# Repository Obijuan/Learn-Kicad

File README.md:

# Learn-Kicad
My notes about Kicad

# WIKI

You can find the Development log in the

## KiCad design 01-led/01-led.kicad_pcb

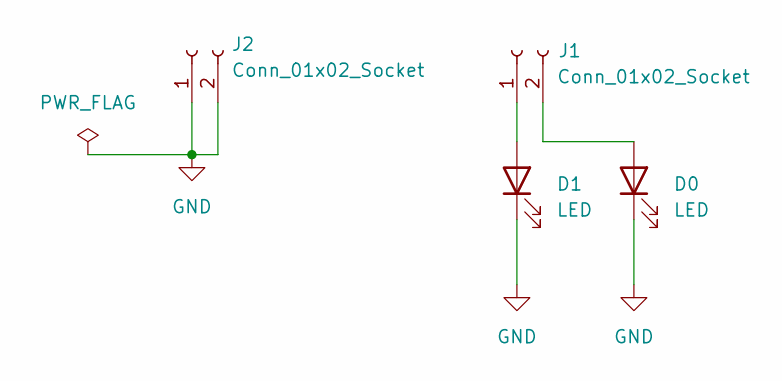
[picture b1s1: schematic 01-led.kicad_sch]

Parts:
D0, D1: LED; LED_THT__LED_D3.0mm
J1, J2: Conn_01x02_Socket; Connector__PinSocket_1x02_P2.54mm_Vertical

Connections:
GND: D0.1 (K), D1.1 (K), J2.1, J2.2
unnamed: D0.2 (A), J1.2
unnamed: D1.2 (A), J1.1

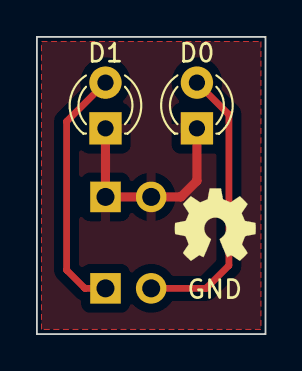
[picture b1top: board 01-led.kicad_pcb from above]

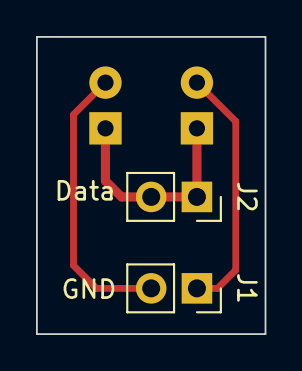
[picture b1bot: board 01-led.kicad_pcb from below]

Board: 2 copper layers, 12.7 x 16.5 mm, 4 parts (2 on the bottom side), 3 nets.

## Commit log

2023-12-28 Add image
2023-12-31 Add 01-led kicad project
2023-12-31 add .gitignore
2024-01-02 01-led: update schematics and pcb
2024-01-02 update image
2024-01-02 01-led: update pcb
2024-01-04 clean up
2024-01-04 led: Update pcb
2024-01-04 led: shorter pin length
2024-01-04 add footprint library
2024-01-04 update library
2024-01-04 update pcb
2024-01-04 update gitignore
2024-01-05 update schematics
2024-01-05 01-led: Connexion to Alhambra-II
2024-01-08 Folder reorganization
2024-01-08 led: change references (D0)
2024-01-08 led: Update freecad model
2024-01-08 LED-01: Clean up
2024-01-08 led: update solder 3D model
2024-01-08 led: update 3D models
2024-01-19 Add certification mark
2024-01-19 update certification mark
2024-01-25 add images
2024-01-25 add animation
